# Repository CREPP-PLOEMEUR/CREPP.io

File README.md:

<!-- ATOC -->
# Sommaire

- [CREPP.io](#crepp.io)
  - [Configuration](#configuration)
  - [Montage de la carte](#montage-de-la-carte)
  - [Programmation de la carte](#programmation-de-la-carte)
  - [Fonctions](#fonctions)
  - [Composants](#composants)
  - [Installation et Utilisation](#installation-et-utilisation)
  - [Auteurs](#auteurs)
  - [Remerciements](#remerciements)

<!-- ATOC -->

# CREPP.io 

Ce projet consiste en la conception et la réalisation de cartes d'extension pour différents modules. La carte permet d'étendre les capacités de certains microcontrôleurs en ajoutant divers connecteurs, composants passifs et actifs, facilitant ainsi le développement de projets IoT (Internet des Objets). Elle est conçue pour offrir une interface facile d'utilisation pour la connexion de capteurs, d'afficheurs, de modules de communication, et d'autres périphériques.

Cette carte est le support de l'atelier Electronique Débutant pour le Club de Robotique et d'Electronique Programmable de Ploemeur (CREPP).

## Configuration

Pour programmer les cartes, nous utiliserons le framework **PlatformIO** 

Les instructions sont disponibles [sur cette page](SETUP.md)

## Montage de la carte 

Il convient tout d'abord de repérer le modèle de votre circuit :
Le numéro de version est sous le QRCode.

Les instructions de montage sont disponibles dans les fichiers suivants : 

- [Montage V1.0](PCB/V1.0/Assembly.md) - Version avec ESP12

- [Montage V1.1](PCB/V1.1/Assembly.md) - Version avec ESP12 amelioré

- [Montage V2.0](PCB/V2.0/Assembly.md) - Version avec Raspberry Pi Pico-(W)

## Programmation de la carte 

- [Codes V1.0](Codes/V1.X) - Code pour ESP12

- [Codes V2.0](Codes/V2.X) - Code pour Rapsberry Pi Pico W
## Fonctions

- **Connectivité étendue :** La carte propose plusieurs connecteurs (PinHeaders, Sockets, Bornes à vis) pour l'intégration facile de différents modules et capteurs.
- **Indicateurs visuels :** Des LEDs sont présentes pour indiquer l'état des signaux.
- **Contrôle manuel :** Des boutons-poussoirs permettent d'interagir directement avec la carte, utile pour des actions comme la navigation dans des menus ou la sélection de modes.
- **Horloge en temps réel :** Un module RTC (DS1307) est intégré pour fournir une mesure précise du temps.
- **Isolation et protection :** Un optocoupleur (PC817) est utilisé pour isoler électriquement certaines parties du circuit.

## Composants

- **Module ESP12 NodeMCU / Raspberry Pi Pico W:** Le cœur du projet
- **Convertisseur ADC (ADS1115) :** Permet des mesures analogiques précises.
- **Horloge RTC (DS1307) :** Fournit une temporisation en temps réel pour les applications nécessitant une précision horaire.
- **Optocoupleur (PC817) :** Assure l'isolation électrique entre différentes sections du circuit.
- **Transistor de puissance (IRF520) :** Gère la distribution de puissance pour les composants plus gourmands en énergie.

Le schéma du circuit et le design du PCB sont réalisés avec KiCad, un logiciel libre de conception de circuits électroniques. Les fichiers sources sont disponibles dans le dossier `/kicad_project`.

## Installation et Utilisation

- **Alimentation 5V ou 3.3V** pour la carte
- **Divers capteurs et modules** selon les besoins du projet (OLED, HC-SR04, BME280, etc.)

1. **Assemblez la carte** en soudant les composants selon le schéma fourni.
2. **Connectez le module** à la carte via les connecteurs dédiés.
3. **Branchez vos capteurs et modules** aux connecteurs correspondants (I2C, SPI, Analogiques, etc.).
5. **Téléversez votre code** sur le module ESP12 NodeMCU pour commencer à utiliser la carte d'extension.

Les contributions sont les bienvenues ! Si vous avez des idées d'amélioration ou des correctifs à proposer, n'hésitez pas à soumettre une Pull Request ou à ouvrir une Issue.

## Auteurs

- **LE GUERROUE Nicolas** - Concepteur principal

## Remerciements

Merci à la communauté open-source et aux contributeurs de KiCad pour avoir fourni les outils nécessaires à la réalisation de ce projet.

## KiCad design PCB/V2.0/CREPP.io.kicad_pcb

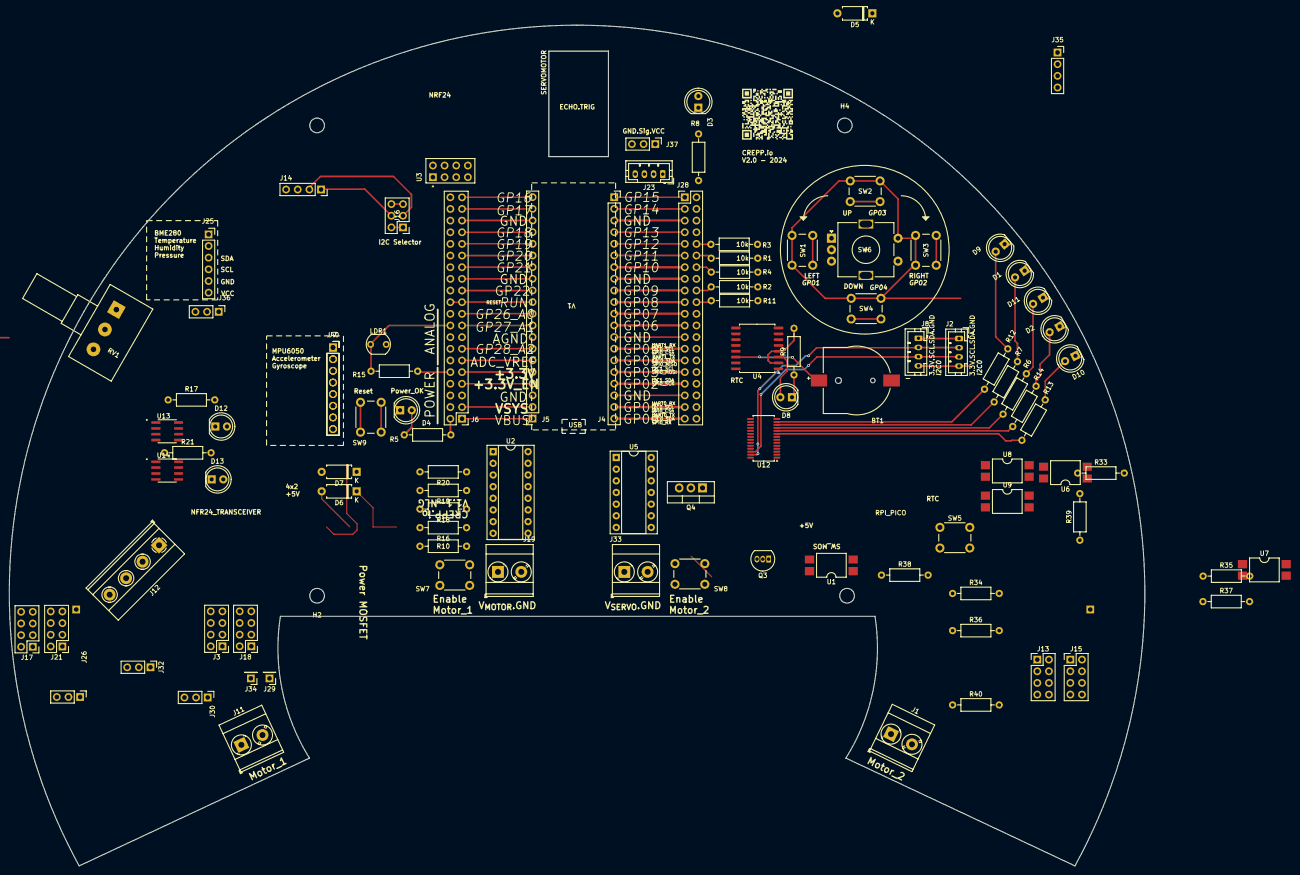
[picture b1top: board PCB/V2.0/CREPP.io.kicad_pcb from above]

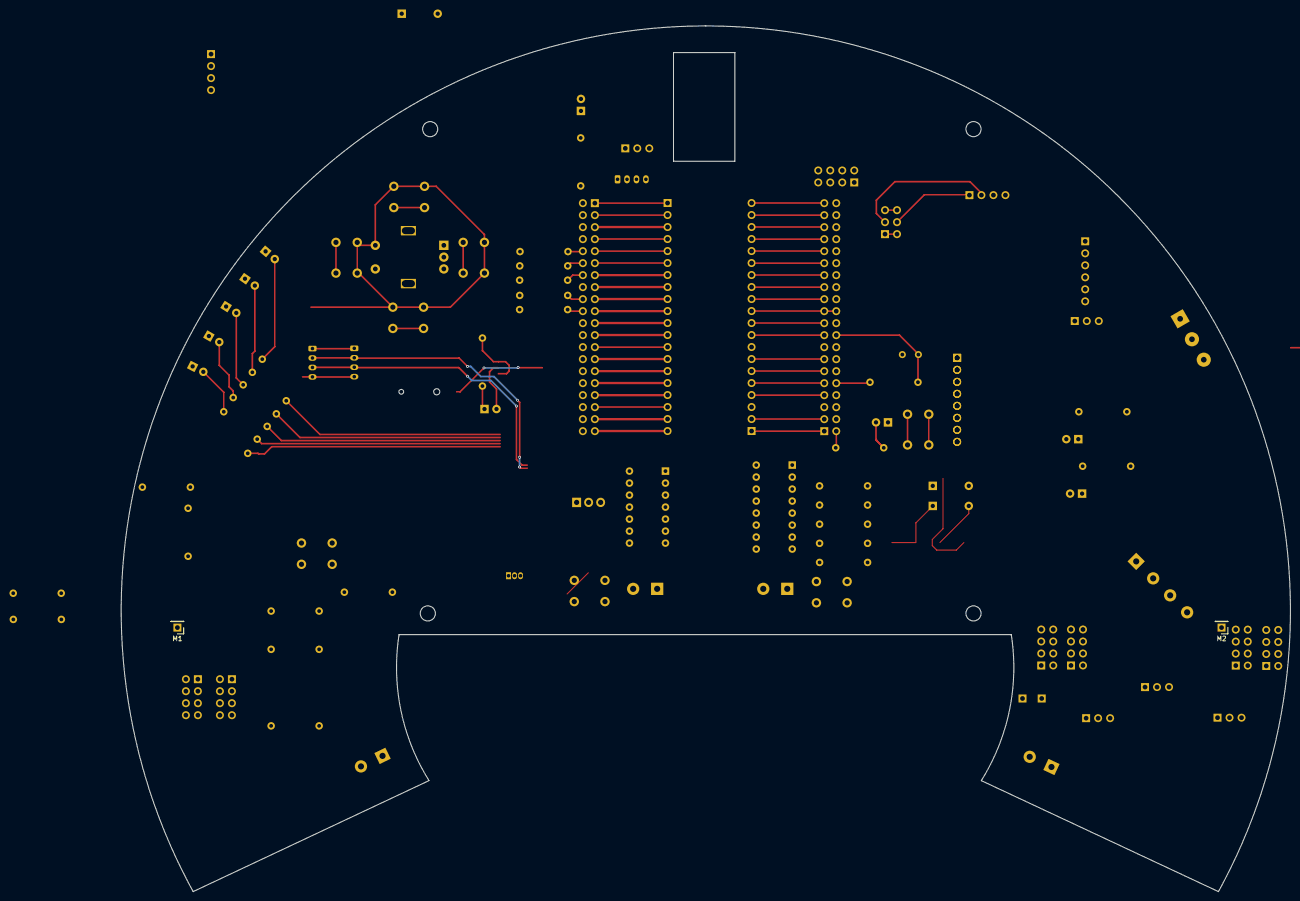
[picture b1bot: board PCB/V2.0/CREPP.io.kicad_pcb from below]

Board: 2 copper layers, 247.5 x 183.2 mm, 144 parts (2 on the bottom side), 124 nets.

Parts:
BT1: Battery_Cell; MPD_BC501SM-TR
D1, D9: LED_Red; LED_D5.0mm_Red
D2, D11: LED_Orange; LED_D5.0mm_Orange
D3, D4, D10: LED_Green; LED_D5.0mm_Green
D5, D6, D7: D; D_A-405_P7.62mm_Horizontal
D8, D12, D13: LED; LED_D5.0mm
H1, H2, H3, H4: MountingHole; MountingHole_3.2mm_M3
J1, J11, J19, J33: Screw_Terminal_01x02; TerminalBlock_Phoenix_MKDS-3-2-5.08_1x02_P5.08mm_Horizontal
J2, J8, J23: Coon_01x04_Pin_2mm; JST_PH_B4B-PH-K_1x04_P2.00mm_Vertical
J3, J13, J15, J17, J18, J21: Conn_02x04_Odd_Even; PinHeader_2x04_P2.54mm_Vertical
J4, J5: Conn_01x20; PinSocket_1x20_P2.54mm_Vertical
J6, J28: Conn_02x20; PinHeader_2x20_P2.54mm_Vertical
J7: VIRTUAL_MPU6050; PinSocket_1x08_P2.54mm_Vertical
J12: Screw_Terminal_01x04; TerminalBlock_Phoenix_MKDS-1,5-4-5.08_1x04_P5.08mm_Horizont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
J14: OLED_SOCKET; PinSocket_1x04_P2.54mm_Vertical
J16: I2C_Selector; PinHeader_2x03_P2.54mm_Vertical
J25: BME; PinSocket_1x06_P2.54mm_Vertical
J26, J30, J37: Servo; PinHeader_1x03_P2.54mm_Vertical
J29, J34: Sig_Servo; PinHeader_1x01_P2.54mm_Vertical
J32: Power_Servo_Selector; PinHeader_1x03_P2.54mm_Vertical
J35: HC-SR04_VIRTUAL; PinSocket_1x04_P2.54mm_Vertical
J36: Power_Selector; PinHeader_1x03_P2.54mm_Vertical
J40: Conn_01x08_Socket; PinSocket_1x08_P2.54mm_Vertical
JP1, JP2, JP3, JP30: Jumper_2.54mm_red
JP4, JP5, JP6, JP7, JP10, JP11, JP12, JP13, JP14, JP15, JP16, JP17, JP18, JP19, JP20, JP21, JP22, JP23, JP24, JP25, JP26, JP27, JP28, JP29: Jumper_2.54mm_green
JP8, JP9: Jumper_2.54mm_blue
LDR1: LDR07; R_LDR_5.1x4.3mm_P3.4mm_Vertical
M1, M2: Motor_DC; PinHeader_1x01_P2.54mm_Vertical
OLED1: SSD1306_OLED_Display_VIRTUAL_128_64
Q3: 2N7002; TO-92_Inline
Q4: IRF520; TO-220-3_Vertical
R1, R2, R3, R4, R11, R15, R16, R20: 10k; R_Axial_DIN0207_L6.3mm_D2.5mm_P10.16mm_Horizontal
R5, R6, R7, R8, R9, R12, R13, R14, R17, R18, R21: 270; R_Axial_DIN0207_L6.3mm_D2.5mm_P10.16mm_Horizontal
R10, R19, R33, R34, R35, R36, R37, R38, R39, R40: 1k; R_Axial_DIN0207_L6.3mm_D2.5mm_P10.16mm_Horizontal
RV1: R_Potentiometer; Potentiometer_Alps_RK163_Single_Horizontal
S1, S2, S3, S4: Spacer_M3_FF_20mm
SERVO_SG1: SG90_Servo
SW1, SW7: SW_Left; SW_PUSH_6mm
SW2: SW_Up; SW_PUSH_6mm
SW3, SW5, SW8: SW_Right; SW_PUSH_6mm
SW4: SW_Down; SW_PUSH_6mm
SW6: RotaryEncoder_Switch; RotaryEncoder
SW9: SW_Reset; SW_PUSH_6mm
U1, U6, U7, U8, U9: PC817_SMD; SMDIP-4_W9.53mm
U2: L293D; DIP-16_W7.62mm_Socket
U3: NRF24L01_Breakout_socket; nRF24L01_Breakout
U4: DS3231M; SOIC-16W_7.5x10.3mm_P1.27mm
U5: 74HC04; DIP-14_W7.62mm_Socket
U10: BME280_Breakout
U11: nRF24L01_Virtual
U12: PCA9635; TSSOP-28_4.4x9.7mm_P0.65mm
U13, U14: ST890
V1: VIRTUAL_FOOTPRINT

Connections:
+3.3V: J2.4, J8.4, J14.3, J17.1, J17.2, J17.3, J17.4, J17.5, J17.6, J17.7, J17.8, J36.1, R9.2, R10.2, R15.1, R18.2, RV1.1, SW1.1, SW2.1, SW3.1, SW4.1, SW6.S2, U3.2 (VCC), U4.2 (VCC), U4.4 (~RST), U12.28 (VDD), U13.6 (OUT), U13.7 (OUT)
+5V: D5.2 (A), J18.1, J18.2, J18.3, J18.4, J18.5, J18.6, J18.7, J18.8, J32.1, J36.3, R5.1, U14.6 (OUT), U14.7 (OUT)
/DEFAULT_LED: J28.8, R8.1
/HC-SR04/ECHO: J23.3, J28.4
/HC-SR04/GND: J23.4, J37.3
/HC-SR04/TRIG: J23.2, J28.2
/IO_Extender/LED_1: R13.1, U12.9 (LED3)
/IO_Extender/LED_2: R14.1, U12.10 (LED4)
/IO_Extender/LED_3: R6.1, U12.11 (LED5)
/IO_Extender/LED_4: R7.1, U12.12 (LED6)
/IO_Extender/LED_5: R12.1, U12.13 (LED7)
/MCU/+3.3V: D12.2 (A), J6.10, J15.2, J15.4, J15.6, J15.8, U13.1 (IN), U13.2 (IN)
/MCU/GND: J6.6, J6.16, J6.26, J6.36, J13.1, J13.3, J13.5, J13.7, J28.6, J28.16, J28.26, J28.36, SW9.2
/MCU/GP0: J28.40, R33.2
/MCU/GP1: J28.38, R35.2
/MCU/GP2: J28.34, R39.2
/MCU/GP3: J28.32, R37.2
/MCU/GP6: J28.24, SW6.B
/MCU/GP7: J28.22, SW6.A
/MCU/GP8: J28.20, R11.1, SW6.S1
/MCU/GP9: J28.18, R2.1, SW2.2
/MCU/GP10: J28.14, R4.1, SW4.2
/MCU/GP11: J28.12, R1.1, SW1.2
/MCU/GP12: J28.10, R3.1, SW3.2
/MCU/GP16: J6.40, U3.7 (MISO)
/MCU/GP17: D7.2 (A), J6.38
/MCU/GP18: J6.34, U3.5 (SCK)
/MCU/GP19: J6.32, U3.6 (MOSI)
/MCU/GP20: J6.30, U3.3 (CE)
/MCU/GP21: J6.28, U3.4 (~CSN)
/MCU/GP26: J6.20, RV1.2
/MCU/GP27: J6.18, LDR1.1, R15.2
/MCU/RUN: J5.11, J6.21, J6.22, SW9.1
/Motors/L239D_Interfaces/5V_Power: D5.1 (K), R34.2, R36.2, R38.2, R40.2, U5.14 (VCC)
/Motors/L239D_Interfaces/DIR_M1_A: U2.2 (1A), U5.2
/Motors/L239D_Interfaces/DIR_M1_B: R34.1, U2.7 (2A), U5.1, U6.4
/Motors/L239D_Interfaces/DIR_M2_A: U2.10 (3A), U5.12
/Motors/L239D_Interfaces/DIR_M2_B: R40.1, U2.15 (4A), U5.13, U8.4
/Motors/L239D_Interfaces/EN_M1_OUT: U2.1 (EN1,2), U5.6
/Motors/L239D_Interfaces/EN_M2_OUT: U2.9 (EN3,4), U5.8
/OLED/A: J14.1, J16.4
/OLED/B: J14.2, J16.3
/Power_Supply1/IN: D13.2 (A), J6.2, U14.1 (IN), U14.2 (IN)
/SCL: J2.3, J8.3, J13.2, J13.4, J13.6, J13.8, J16.5, J16.6, J25.4, J28.28, J40.4, U4.16 (SCL), U12.26 (SCL)
/SDA: J2.2, J8.2, J15.1, J15.3, J15.5, J15.7, J16.1, J16.2, J25.3, J28.30, J40.3, U4.15 (SDA), U12.27 (SDA)
/SERVO_1: J37.2, U12.6 (LED0)
/Sensors/VCC_Sensor: J25.6, J36.2
/Servo_Power/Ext_Servo: J32.3, J33.1
GND: BT1.2 (-), D1.1 (K), D2.1 (K), D3.1 (K), D4.1 (K), D9.1 (K), D10.1 (K), D11.1 (K), J2.1, J3.1, J3.2, J3.3, J3.4, J3.5, J3.6, J3.7, J3.8, J8.1, J12.4, J14.4, J21.1, J21.2, J21.3, J21.4, J21.5, J21.6, J21.7, J21.8, J25.5, J26.3, J30.3, J33.2, LDR1.2, Q4.3 (S), R1.2, R2.2, R3.2, R4.2, R11.2, R20.2, RV1.3, SW5.2, SW6.C, SW8.2, U1.3, U3.1 (GND), U4.5 (GND), U4.6 (GND), U4.7 (GND), U4.8 (GND), U4.9 (GND), U4.10 (GND), U4.11 (GND), U4.12 (GND), U4.13 (GND), U6.2, U6.3, U7.2, U7.3, U8.2, U8.3, U9.2, U9.3, U12.14 (VSS), U13.3 (~ON), U13.4 (GND), U14.3 (~ON), U14.4 (GND)
GND_MOS: Q3.1 (S), R16.1, U1.2
GND_POWER: U2.4 (GND), U2.5 (GND), U2.12 (GND), U2.13 (GND), U5.7 (GND)
unnamed: BT1.1 (+), U4.14 (VBAT)
unnamed: D1.2 (A), R7.2
unnamed: D2.2 (A), R14.2
unnamed: D3.2 (A), R8.2
unnamed: D4.2 (A), R5.2
unnamed: D6.2 (A), J12.3, Q4.2 (D)
unnamed: D6.1 (K), J12.1, J12.2, R19.1
unnamed: D7.1 (K), Q3.2 (G), R16.2, SW7.1
unnamed: D8.2 (A), U4.3 (~INT/SQW)
unnamed: D8.1 (K), R9.1
unnamed: D9.2 (A), R12.2
unnamed: D10.2 (A), R13.2
unnamed: D11.2 (A), R6.2
unnamed: D12.1 (K), R17.1
unnamed: D13.1 (K), R21.1
unnamed: J1.1, U2.3 (1Y)
unnamed: J1.2, U2.6 (2Y)
unnamed: J5.1, J6.1
unnamed: J5.2, J6.3
unnamed: J5.3, J6.5
unnamed: J5.4, J6.7
unnamed: J5.5, J6.9
unnamed: J5.6, J6.11
unnamed: J5.7, J6.13
unnamed: J5.8, J6.15
unnamed: J5.9, J6.17
unnamed: J5.10, J6.19
unnamed: J5.12, J6.23
unnamed: J5.13, J6.25
unnamed: J5.14, J6.27
unnamed: J5.15, J6.29
unnamed: J5.16, J6.31
unnamed: J5.17, J6.33
unnamed: J5.18, J6.35
unnamed: J5.19, J6.37
unnamed: J5.20, J6.39
unnamed: J11.1, U2.11 (3Y)
unnamed: J11.2, U2.14 (4Y)
unnamed: J19.1, U2.8 (VCC2), U2.16 (VCC1)
unnamed: J26.1, J29.1
unnamed: J26.2, J30.2, J32.2
unnamed: J4.1, J28.1
unnamed: J4.2, J28.3
unnamed: J4.3, J28.5
unnamed: J4.4, J28.7
unnamed: J4.5, J28.9
unnamed: J4.6, J28.11
unnamed: J4.7, J28.13
unnamed: J4.8, J28.15
unnamed: J4.9, J28.17
unnamed: J4.10, J28.19
unnamed: J4.11, J28.21
unnamed: J4.12, J28.23
unnamed: J4.13, J28.25
unnamed: J4.14, J28.27
unnamed: J4.15, J28.29
unnamed: J4.16, J28.31
unnamed: J4.17, J28.33
unnamed: J4.18, J28.35
unnamed: J4.19, J28.37
unnamed: J4.20, J28.39
unnamed: J30.1, J34.1
unnamed: Q3.3 (D), R18.1, U1.1
unnamed: Q4.1 (G), R19.2, R20.1, U1.4
unnamed: R10.1, SW7.2
unnamed: R33.1, U6.1
unnamed: R35.1, U7.1
unnamed: R36.1, SW8.1, U5.5, U7.4
unnamed: R37.1, U9.1
unnamed: R38.1, SW5.1, U5.9, U9.4
unnamed: R39.1, U8.1
unnamed: R17.2, U13.8 (~FAULT)
unnamed: R21.2, U14.8 (~FAULT)

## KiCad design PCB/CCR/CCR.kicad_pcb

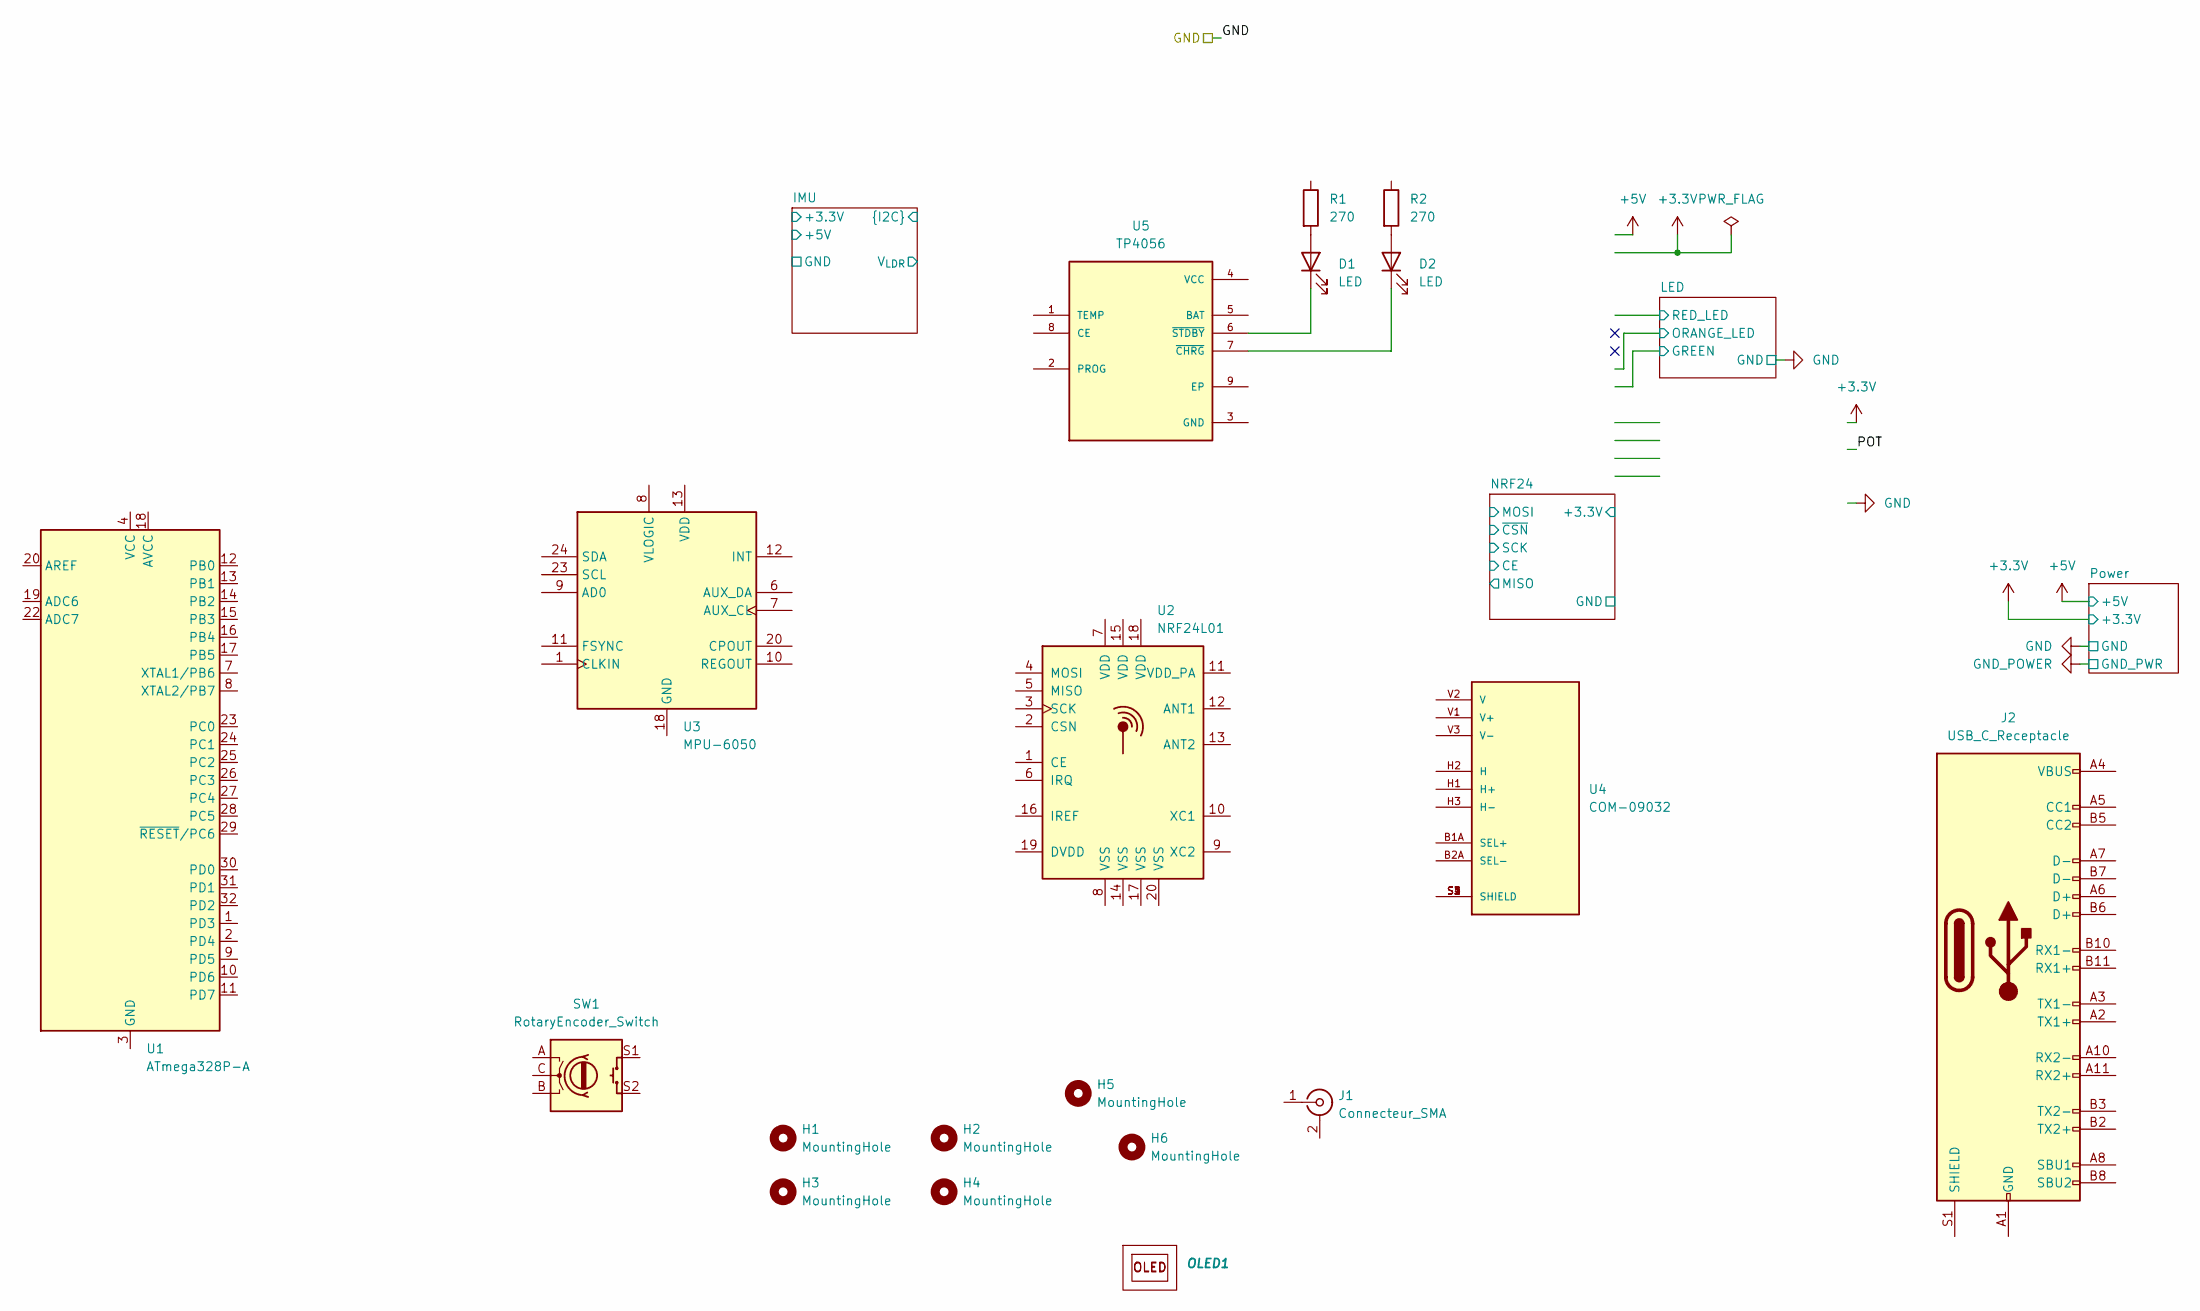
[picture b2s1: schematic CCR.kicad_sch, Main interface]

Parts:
D1, D2: LED; LED_0603_1608Metric
H1, H2, H3, H4, H5, H6: MountingHole; MountingHole_3.2mm_M3
J1: Connecteur_SMA; SMA_Amphenol_132289_EdgeMount
J2: USB_C_Receptacle; USB_C_Receptacle_GCT_USB4085
OLED1: SSD1306_OLED_Display_VIRTUAL_128_64
R1, R2: 270; R_0603_1608Metric
SW1: RotaryEncoder_Switch; RotaryEncoder
U1: ATmega328P-A; TQFP-32_7x7mm_P0.8mm
U2: NRF24L01; QFN-20-1EP_4x4mm_P0.5mm_EP2.5x2.5mm
U3: MPU-6050; InvenSense_QFN-24_4x4mm_P0.5mm
U4: COM-09032; XDCR_COM-09032; PARTREV N/A
U5: TP4056; SOP127P600X175-9N

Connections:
unnamed: D1.2 (A), R1.2
unnamed: D1.1 (K), U5.6 (~STDBY)
unnamed: D2.2 (A), R2.2
unnamed: D2.1 (K), U5.7 (~CHRG)
unnamed: J2.A1 (GND), J2.A12 (GND), J2.B1 (GND), J2.B12 (GND)
unnamed: J2.A4 (VBUS), J2.A9 (VBUS), J2.B4 (VBUS), J2.B9 (VBUS)
unnamed: U1.3 (GND), U1.5 (GND), U1.21 (GND)
unnamed: U1.4 (VCC), U1.6 (VCC)
unnamed: U4.S1 (SHIELD), U4.S2 (SHIELD), U4.S3 (SHIELD), U4.S4 (SHIELD)

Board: 2 copper layers, 20 parts (1 on the bottom side), 9 nets, no tracks yet.

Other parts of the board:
V1: VIRTUAL_FOOTPRINT

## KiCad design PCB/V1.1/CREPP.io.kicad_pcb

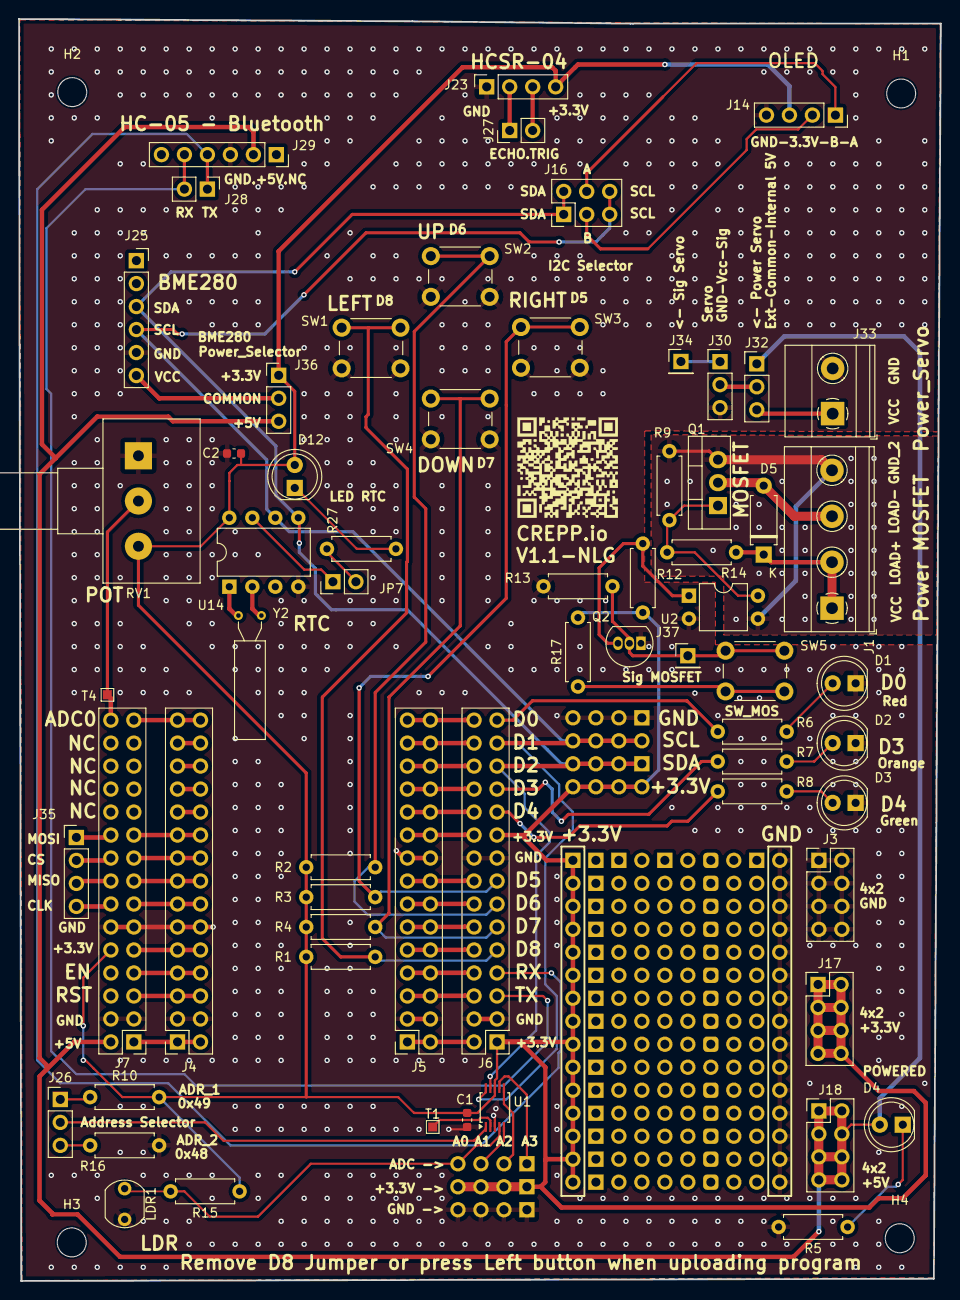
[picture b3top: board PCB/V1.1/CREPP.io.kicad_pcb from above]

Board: 2 copper layers, 101.9 x 139.4 mm, 78 parts (0 on the bottom side), 77 nets.

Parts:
C1, C2: 100nF; C_0603_1608Metric
D1, D2, D3, D4, D12: LED; LED_D5.0mm
D5: D; D_A-405_P7.62mm_Horizontal
H1, H2, H3, H4: MountingHole; MountingHole_3.2mm_M3
J1: Screw_Terminal_01x04; TerminalBlock_Phoenix_MKDS-1,5-4-5.08_1x04_P5.08mm_Horizont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
J3, J13, J15, J17, J18: Conn_02x04_Odd_Even; PinHeader_2x04_P2.54mm_Vertical
J4, J5: Right_Connector; PinSocket_2x15_P2.54mm_Vertical
J6, J8, J9, J10, J11, J12: Right_Connector; PinHeader_2x15_P2.54mm_Vertical
J7: Left_Connector; PinHeader_2x15_P2.54mm_Vertical
J14: OLED_SOCKET; PinSocket_1x04_P2.54mm_Vertical
J16: I2C_Selector; PinHeader_2x03_P2.54mm_Vertical
J19: Analog_Inputs; PinHeader_1x04_P2.54mm_Vertical
J20: GND_Analog; PinHeader_1x04_P2.54mm_Vertical
J21: +3.3V_Analog; PinHeader_1x04_P2.54mm_Vertical
J23: HC-SR; PinSocket_1x04_P2.54mm_Vertical
J25: BME; PinSocket_1x06_P2.54mm_Vertical
J26: Addr_Selector; PinHeader_1x03_P2.54mm_Vertical
J27: SIG_HCSR04; PinHeader_1x02_P2.54mm_Vertical
J28: SIG_HC-05; PinHeader_1x02_P2.54mm_Vertical
J29: Conn_01x06_Socket; PinSocket_1x06_P2.54mm_Vertical
J30: Servo; PinHeader_1x03_P2.54mm_Vertical
J32: Power_Servo_Selector; PinHeader_1x03_P2.54mm_Vertical
J33: Screw_Terminal_01x02; TerminalBlock_Phoenix_MKDS-1,5-2_1x02_P5.00mm_Horizontal
J34: Sig_Servo; PinHeader_1x01_P2.54mm_Vertical
J35: SPI_Connector; PinHeader_1x04_P2.54mm_Vertical
J36: Power_Selector; PinHeader_1x03_P2.54mm_Vertical
J37: Sig_MOSFET; PinHeader_1x01_P2.54mm_Vertical
JP7: Jumper; PinHeader_1x02_P2.54mm_Vertical
LDR1: LDR07; R_LDR_5.1x4.3mm_P3.4mm_Vertical
Q1: IRF520; TO-220-3_Vertical
Q2: 2N7000; TO-92_Inline
R1, R2, R3, R4, R9, R10, R13, R15, R16: 10k; R_Axial_DIN0207_L6.3mm_D2.5mm_P7.62mm_Horizontal
R5, R6, R7, R8, R12, R27: 270; R_Axial_DIN0207_L6.3mm_D2.5mm_P7.62mm_Horizontal
R14, R17: 1k; R_Axial_DIN0207_L6.3mm_D2.5mm_P7.62mm_Horizontal
RV1: R_Potentiometer; Potentiometer_Alps_RK163_Single_Horizontal
SW1, SW5: SW_Left; SW_PUSH_6mm
SW2: SW_Up; SW_PUSH_6mm
SW3: SW_Right; SW_PUSH_6mm
SW4: SW_Down; SW_PUSH_6mm
T1, T4: TestPoint; TestPoint_Pad_1.0x1.0mm
U1: ADS1115IDGS; TSSOP-10_3x3mm_P0.5mm
U2: PC817; DIP-4_W7.62mm
U14: DS1307+; DIP-8_W7.62mm
Y2: 16MHz; Crystal_AT310_D3.0mm_L10.0mm_Horizontal

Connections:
+3.3V: C1.1, C2.1, D12.2 (A), J6.1, J6.19, J7.10, J12.1, J12.3, J12.5, J12.7, J12.9, J12.11, J12.13, J12.15, J12.17, J12.19, J12.21, J12.23, J12.25, J12.27, J12.29, J14.3, J15.2, J15.4, J15.6, J15.8, J17.1, J17.2, J17.3, J17.4, J17.5, J17.6, J17.7, J17.8, J21.1, J21.2, J21.3, J21.4, J23.4, J36.1, R1.1, R2.1, R3.1, R4.1, R10.2, R12.2, R15.1, R17.2, RV1.3, U1.8 (VDD), U14.8 (VCC)
+5V: D4.2 (A), J7.2, J18.1, J18.2, J18.3, J18.4, J18.5, J18.6, J18.7, J18.8, J29.2, J32.1, J36.3
/Bluetooth/RX: J6.7, J28.1, J29.4
/Bluetooth/TX: J6.5, J28.2, J29.5
/IO_Extender/A1: J19.3, U1.5 (AIN1)
/IO_Extender/A2: J19.2, U1.6 (AIN2)
/IO_Extender/A3: J19.1, U1.7 (AIN3)
/IO_Extender/SCL: J6.27, J13.2, J13.4, J13.6, J13.8, J16.5, J16.6, J25.4, U1.10 (SCL), U14.6 (SCL)
/IO_Extender/SDA: J6.25, J15.1, J15.3, J15.5, J15.7, J16.1, J16.2, J25.3, U1.9 (SDA), U14.5 (SDA)
/LDR: J19.4, LDR1.1, R15.2, U1.4 (AIN0)
/LED/GREEN: J6.21, R8.1
/LED/ORANGE_LED: J6.23, R7.1
/LED/RED_LED: J6.29, R6.1
/MCU/CLK: J7.14, J35.4
/MCU/CS: J7.18, J35.2
/MCU/GPIO12_D6: J6.13, R2.2, SW2.1
/MCU/GPIO13_D7_RX2: J6.11, R4.2, SW4.1
/MCU/GPIO14_D5: J6.15, R3.2, SW3.1
/MCU/GPIO15_D8_TX2: J6.9, R1.2, SW1.1
/MCU/MISO: J7.16, J35.3
/MCU/MOSI: J7.20, J35.1
/MCU/Pin_1: J4.1, J4.2, J7.1
/MCU/Pin_2: J5.1, J5.2, J6.2
/MCU/Pin_5: J4.5, J4.6, J7.5
/MCU/Pin_6: J5.5, J5.6, J6.6
/MCU/Pin_7: J4.7, J4.8, J7.7
/MCU/Pin_8: J5.7, J5.8, J6.8
/MCU/Pin_9: J4.9, J4.10, J7.9
/MCU/Pin_10: J5.9, J5.10, J6.10
/MCU/Pin_12: J5.11, J5.12, J6.12
/MCU/Pin_13: J4.13, J4.14, J7.13
/MCU/Pin_14: J5.13, J5.14, J6.14
/MCU/Pin_15: J4.15, J4.16, J7.15
/MCU/Pin_16: J5.15, J5.16, J6.16
/MCU/Pin_17: J4.17, J4.18, J7.17
/MCU/Pin_19: J4.19, J4.20, J7.19
/MCU/Pin_20: J5.19, J5.20, J6.20
/MCU/Pin_21: J4.21, J4.22
/MCU/Pin_22: J5.21, J5.22, J6.22
/MCU/Pin_23: J4.23, J4.24
/MCU/Pin_24: J5.23, J5.24, J6.24
/MCU/Pin_25: J4.25, J4.26
/MCU/Pin_26: J5.25, J5.26, J6.26
/MCU/Pin_27: J4.27, J4.28
/MCU/Pin_28: J5.27, J5.28, J6.28
/MCU/Pin_29: J4.29, J4.30, J7.29
/MCU/Pin_30: J5.29, J5.30, J6.30
/OLED/A: J14.1, J16.4
/OLED/B: J14.2, J16.3
/POT: J7.30, RV1.2, T4.1
/Power/Ext_Servo: J32.3, J33.1
/Sensors/VCC_Sensor: J25.6, J36.2
GND: C1.2, C2.2, D1.1 (K), D2.1 (K), D3.1 (K), J3.1, J3.2, J3.3, J3.4, J3.5, J3.6, J3.7, J3.8, J4.3, J4.4, J4.11, J4.12, J5.3, J5.4, J5.17, J5.18, J6.3, J6.4, J6.17, J6.18, J7.3, J7.4, J7.11, J7.12, J8.2, J8.4, J8.6, J8.8, J8.10, J8.12, J8.14, J8.16, J8.18, J8.20, J8.22, J8.24, J8.26, J8.28, J8.30, J13.1, J13.3, J13.5, J13.7, J14.4, J20.1, J20.2, J20.3, J20.4, J23.1, J25.5, J29.3, J30.3, J33.2, LDR1.2, Q2.1 (S), R5.2, R13.1, R16.2, RV1.1, SW1.2, SW2.2, SW3.2, SW4.2, U1.3 (GND), U2.2, U14.4 (GND)
GND_POWER: J1.4, Q1.3 (S), R9.2, U2.3
unnamed: D1.2 (A), R6.2
unnamed: D2.2 (A), R7.2
unnamed: D3.2 (A), R8.2
unnamed: D4.1 (K), R5.1
unnamed: D5.2 (A), J1.3, Q1.2 (D)
unnamed: D5.1 (K), J1.1, J1.2, R14.1
unnamed: D12.1 (K), R27.1
unnamed: J23.2, J27.1
unnamed: J23.3, J27.2
unnamed: J26.1, R10.1
unnamed: J26.2, U1.1 (ADDR)
unnamed: J26.3, R16.1
unnamed: J30.1, J34.1
unnamed: J30.2, J32.2
unnamed: J37.1, Q2.2 (G), R13.2, SW5.1
unnamed: JP7.1 (A), U14.7 (SQW/OUT)
unnamed: JP7.2 (B), R27.2
unnamed: Q1.1 (G), R9.1, R14.2, U2.4
unnamed: Q2.3 (D), R12.1, U2.1
unnamed: R17.1, SW5.2
unnamed: T1.1, U1.2 (ALERT/RDY)
unnamed: U14.1 (X1), Y2.1
unnamed: U14.2 (X2), Y2.2

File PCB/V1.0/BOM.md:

# Bill of Materials (BOM)

| Référence | Quantité | Désignation |
|-----------|----------|-------------|
| R7,R27,R5,R12,R6,R8 | 6 | 270 |
| J25 | 1 | BME |
| RV1 | 1 | R_Potentiometer |
| J20 | 1 | GND_Analog |
| J30 | 1 | Servo |
| J13,J15,J17,J3,J18 | 5 | Conn_02x04_Odd_Even |
| D3,D1,D12,D4,D2 | 5 | LED |
| SW4 | 1 | SW_Down |
| J4,J5 | 2 | Right_Connector |
| J19 | 1 | Analog_Inputs |
| J16 | 1 | I2C_Selector |
| J6,J12,J8,J9,J11,J10 | 6 | Right_Connector |
| J7 | 1 | Left_Connector |
| JP7 | 1 | Jumper |
| J33 | 1 | Screw_Terminal_01x02 |
| SW2 | 1 | SW_Up |
| R1,R2,R3,R16,R15,R4,R9,R10 | 8 | 10k |
| J23 | 1 | HC-SR |
| T1,T4 | 2 | TestPoint |
| J21 | 1 | +3.3V_Analog |
| U2 | 1 | PC817 |
| J35 | 1 | SPI_Connector |
| SW3 | 1 | SW_Right |
| D5 | 1 | D |
| U1 | 1 | ADS1115IDGS |
| J29 | 1 | Conn_01x06_Socket |
| J36 | 1 | Power_Selector |
| J24 | 1 | BME_VIRTUAL |
| J26 | 1 | Addr_Selector |
| J37 | 1 | Sig_MOSFET |
| J1 | 1 | Screw_Terminal_01x04 |
| C17 | 1 | 100nF |
| J32 | 1 | Power_Servo_Selector |
| J27 | 1 | SIG_HCSR04 |
| Y2 | 1 | 16MHz |
| Q1 | 1 | IRF520 |
| SW1 | 1 | SW_Left |
| C1 | 1 | 100nF |
| J14 | 1 | OLED_SOCKET |
| J28 | 1 | SIG_HC-05 |
| R11 | 1 | R11 |
| J34 | 1 | Sig_Servo |
| R14 | 1 | 1k |
| U14 | 1 | DS1307+ |

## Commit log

2024-08-29 Update of README
2024-09-15 Update of doc
2024-09-15 Update of changelog
2024-09-27 Update codes for LED and Potentiometer
2024-09-27 Update code
2024-09-30 Update of Doc, add code for buttons
2024-10-06 Add V1.1
2024-10-06 Test URl MD
2024-10-06 Add md list
2024-10-06 Add Assembly file
2024-10-06 Add file src
2024-10-06 Add TOC
2024-10-06 Add TCO readme.md
2024-10-06 TOC generated automatically
2024-10-06 Udpate
2024-10-06 Update TOC
2024-10-13 update of directory
2024-10-17 Add code
2024-11-12 Update BME and OLED
2024-11-14 Update 2.0 - IMU and NRF24 support
2024-11-19 Add RTC
2024-11-22 Add codes
2024-11-22 Try git library
2024-11-22 Add scanner
2024-11-22 Add lib - try again
2024-11-22 Add CREPP_Lib handler
2024-11-23 Update of code
2024-12-31 Update V2.0 form factor
2025-01-01 Add img
2025-01-02 Add Crepp COntrol Remote
2025-01-18 Update of BME and OLED
2025-01-19 Add licence file
2025-02-07 Update board
